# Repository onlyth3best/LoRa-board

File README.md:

# LoRa-board
built with help from stasis.hackclub.com…
<br/>

### What is this?
LoRa stands for 'Long Range', usually to transmit things like with radio. This particular project is such a LoRa board, with:
- an ESP32-S3
- a SX1262 radio
- a U.FL antenna

[lorarpdff.pdf](https://github.com/user-attachments/files/29169228/lorarpdff.pdf)

## how does it work? //Setup
So, the board gains power from the USB-C receptacle, there's also a couple buttons with the EN-RESET and GPIO10-BOOT functionalities respectively. What you need to do, once you get the board, is to boot it-- then, download the Meshtastic app and try to pair the LoRa board with your device just like that… no firmware is needed, afaik… :D

the references for each pin are in the BOM, like:
C1,C3,C4,C5 == Capacitor_SMD:C_0402_1005Metric
C2,C6,C7 == Capacitor_SMD:C_0402_1005Metric
J1 == Connector_USB:USB_C_Receptacle_HRO_TYPE-C-31-M-12
L1 == Inductor_SMD:L_6.3x6.3_H3
R1,R2 == Resistor_SMD:R_0201_0603Metric
R3,R4 == Resistor_SMD:R_0402_1005Metric
SW1,SW2 == Button_Switch_Keyboard:SW_Cherry_MX_2.00u_PCB
U1 == ESP32-S3-WROOM-1
U2 == AMS1117-3.3
U3 == SX1262IMLTRT

## why did I make it?
I made this project because I think it'd be really cool to have something that can transmit messages via a radio (especially with a friend)!

[lora.pdf](https://github.com/user-attachments/files/28474012/lora.pdf)

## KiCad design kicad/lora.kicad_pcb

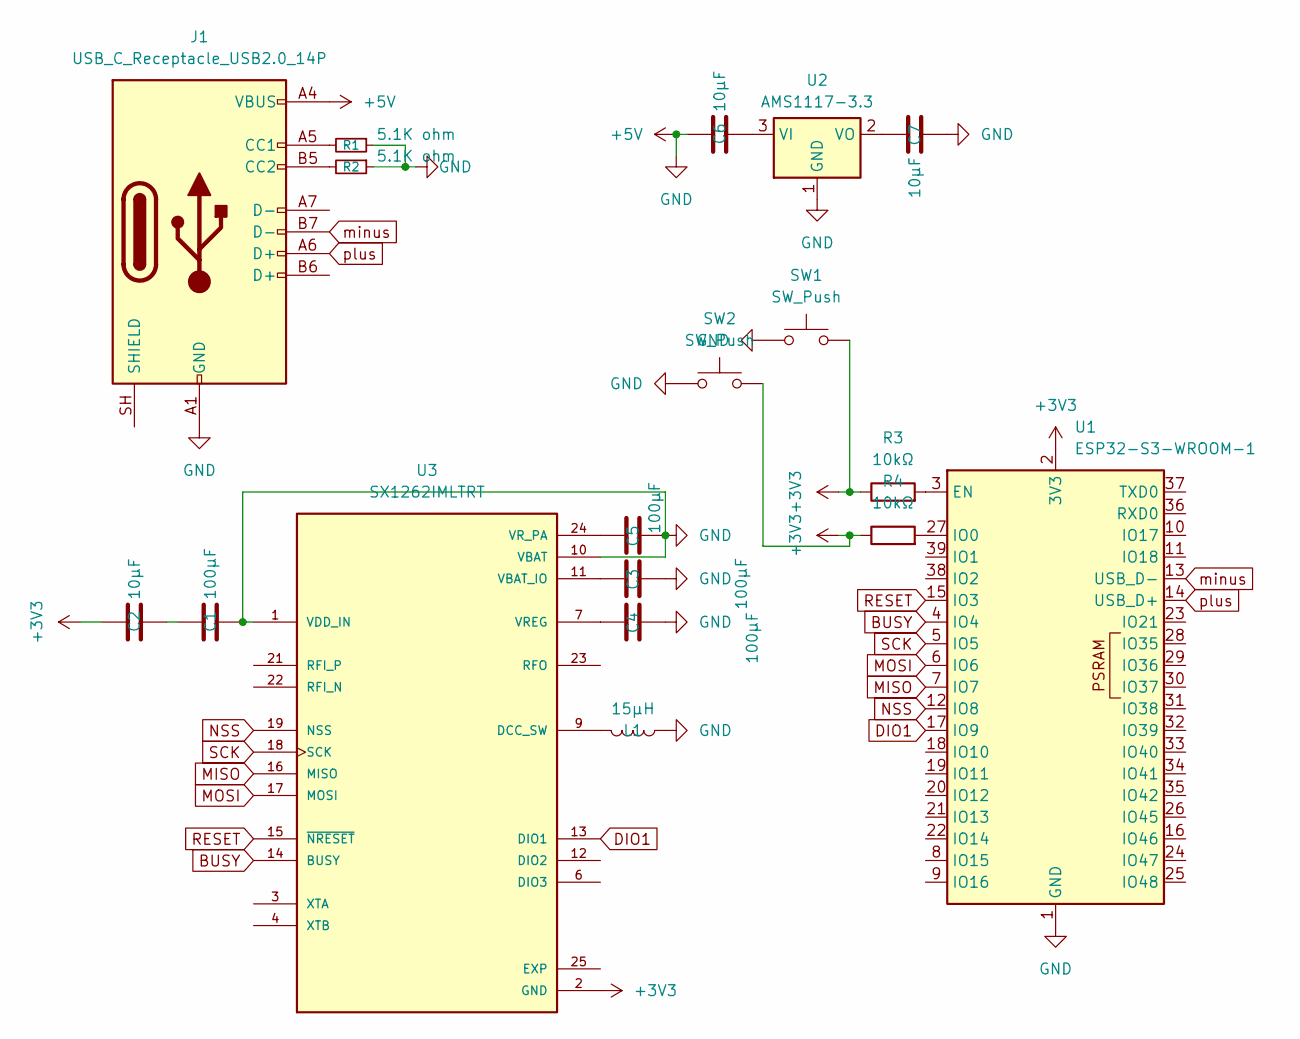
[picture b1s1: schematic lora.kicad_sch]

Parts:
C1, C3, C4, C5: 100µF; C_0402_1005Metric
C2, C6, C7: 10µF; C_0402_1005Metric
J1: USB_C_Receptacle_USB2.0_14P; USB_C_Receptacle_HRO_TYPE-C-31-M-12
L1: 15µH; L_6.3x6.3_H3
R1, R2: 5.1K ohm; R_0201_0603Metric
R3, R4: 10kΩ; R_0402_1005Metric
SW1, SW2: SW_Push; SW_Cherry_MX_2.00u_PCB
U1: ESP32-S3-WROOM-1
U2: AMS1117-3.3; SOT-223-3_TabPin2
U3: SX1262IMLTRT; QFN50P400X400X100-25N; PARTREV 1.1

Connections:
BUSY: U1.4 (IO4), U3.14 (BUSY)
DIO1: U1.17 (IO9), U3.13 (DIO1)
MISO: U1.7 (IO7), U3.16 (MISO)
MOSI: U1.6 (IO6), U3.17 (MOSI)
NSS: U1.12 (IO8), U3.19 (NSS)
unnamed: C1.1, C2.2
unnamed: J1.A5 (CC1), R1.2
unnamed: J1.B5 (CC2), R2.2
unnamed: R3.2, U1.3 (EN)
unnamed: R4.2, U1.27 (IO0)
unnamed: C6.2, U2.3 (VI)
unnamed: C7.2, U2.2 (VO)
unnamed: L1.2, U3.9 (DCC_SW)
unnamed: C3.2, U3.11 (VBAT_IO)
unnamed: C4.2, U3.7 (VREG)
unnamed: C5.2, U3.24 (VR_PA)
RESET: U1.15 (IO3), U3.15 (~NRESET)
SCK: U1.5 (IO5), U3.18 (SCK)
minus: J1.B7 (D-), U1.13 (USB_D-)
plus: J1.A6 (D+), U1.14 (USB_D+)

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
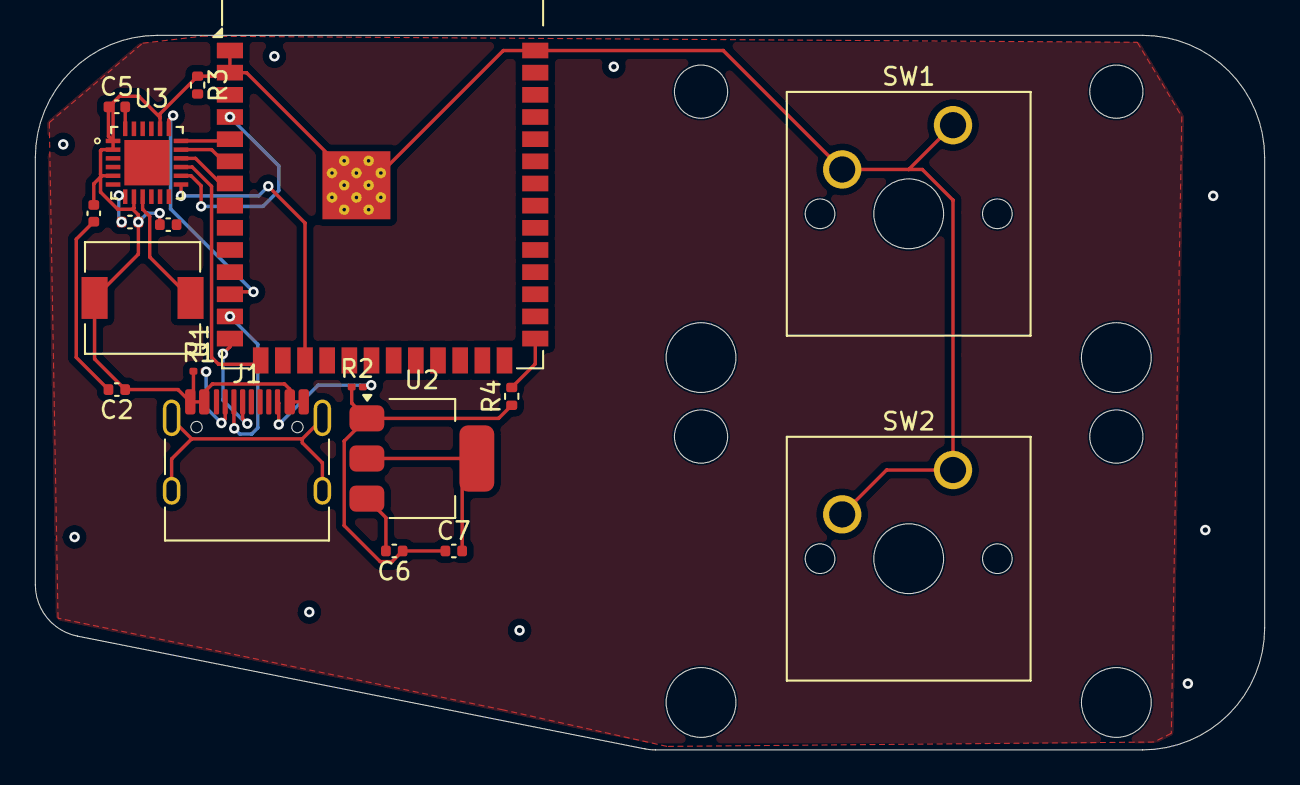
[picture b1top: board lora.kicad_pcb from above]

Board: 2 copper layers, 70.5 x 40.9 mm, 18 parts (0 on the bottom side), 21 nets.

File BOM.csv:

"Reference","Qty","Value","DNP","Exclude from BOM","Exclude from Board","Footprint","Datasheet"
"C1,C3,C4,C5","4","100µF","","","","Capacitor_SMD:C_0402_1005Metric",""
"C2,C6,C7","3","10µF","","","","Capacitor_SMD:C_0402_1005Metric",""
"J1","1","USB_C_Receptacle_USB2.0_14P","","","","Connector_USB:USB_C_Receptacle_HRO_TYPE-C-31-M-12","https://www.usb.org/sites/default/files/documents/usb_type-c.zip"
"L1","1","15µH","","","","Inductor_SMD:L_6.3x6.3_H3",""
"R1,R2","2","5.1K ohm","","","","Resistor_SMD:R_0201_0603Metric",""
"R3,R4","2","10kΩ","","","","Resistor_SMD:R_0402_1005Metric",""
"SW1,SW2","2","SW_Push","","","","Button_Switch_Keyboard:SW_Cherry_MX_2.00u_PCB",""
"U1","1","ESP32-S3-WROOM-1","","","","RF_Module:ESP32-S3-WROOM-1","https://www.espressif.com/sites/default/files/documentation/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"
"U2","1","AMS1117-3.3","","","","Package_TO_SOT_SMD:SOT-223-3_TabPin2","http://www.advanced-monolithic.com/pdf/ds1117.pdf"
"U3","1","SX1262IMLTRT","","","","footprints:QFN50P400X400X100-25N",""

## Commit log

2026-06-01 Create test
2026-06-01 Create testik
2026-06-01 Create teesttikk
